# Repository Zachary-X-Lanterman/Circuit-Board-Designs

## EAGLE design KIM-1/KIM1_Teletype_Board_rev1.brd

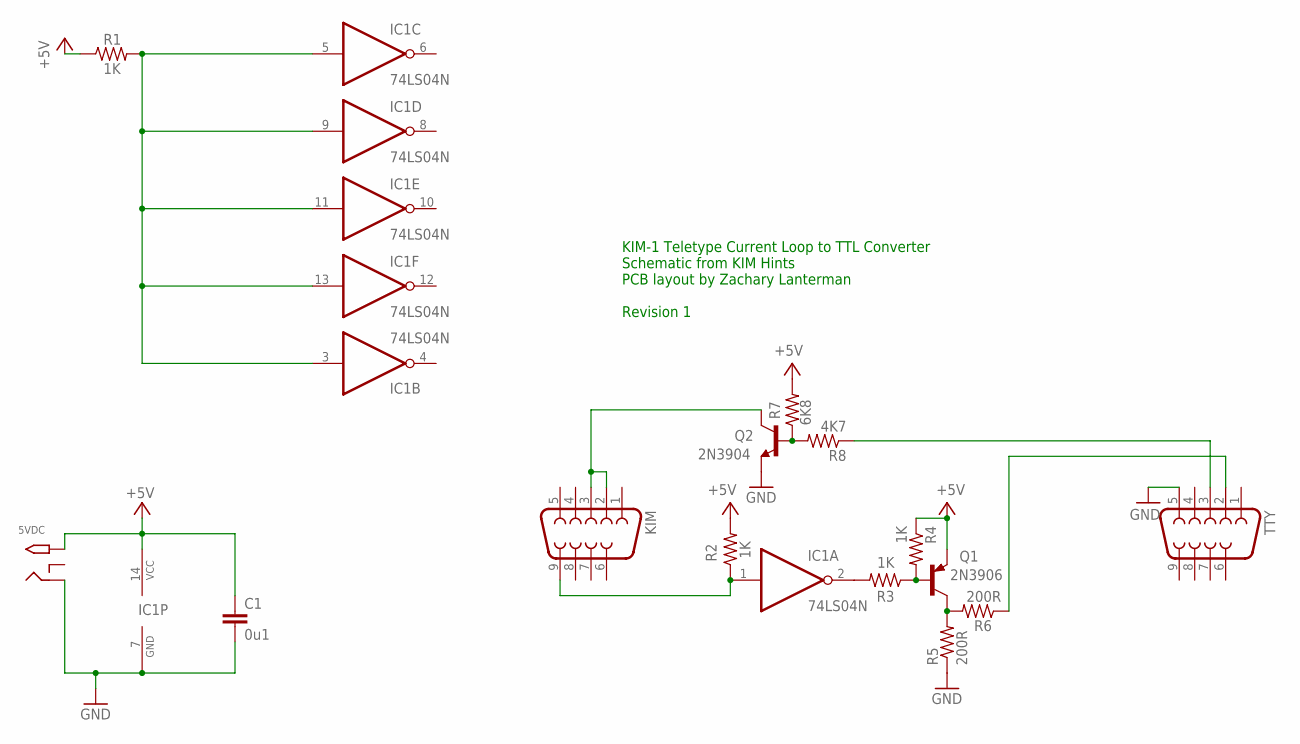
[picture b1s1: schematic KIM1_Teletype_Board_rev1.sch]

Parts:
5VDC: 2.1MMJACKTHM; PJ-102A
C1: 0u1; C050-025X075-AARON
IC1: 74LS04N; DIL14
KIM: F09HP
Q1: 2N3906; TO92
Q2: 2N3904; TO92
R1, R2, R3, R4: 1K; 0207/10
R5, R6: 200R; 0207/10
R7: 6K8; 0207/10
R8: 4K7; 0207/10
TTY: F09HP

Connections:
+5V: 5VDC.TIP, C1.1, IC1.14 (VCC), Q1.3 (E), R1.1, R2.2, R4.1, R7.2
GND: 5VDC.RING, C1.2, IC1.7 (GND), Q2.3 (E), R5.1, TTY.5
unnamed: IC1.2 (O), R3.2
unnamed: Q1.2 (B), R3.1, R4.2
unnamed: Q1.1 (C), R5.2, R6.2
unnamed: IC1.3 (I), IC1.5 (I), IC1.9 (I), IC1.11 (I), IC1.13 (I), R1.2
unnamed: R6.1, TTY.2
unnamed: KIM.2, KIM.3, Q2.1 (C)
unnamed: Q2.2 (B), R7.1, R8.2
unnamed: R8.1, TTY.3
U: IC1.1 (I), KIM.9, R2.1

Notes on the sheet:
KIM-1 Teletype Current Loop to TTL Converter Schematic from KIM Hints PCB layout by Zachary Lanterman Revision 1

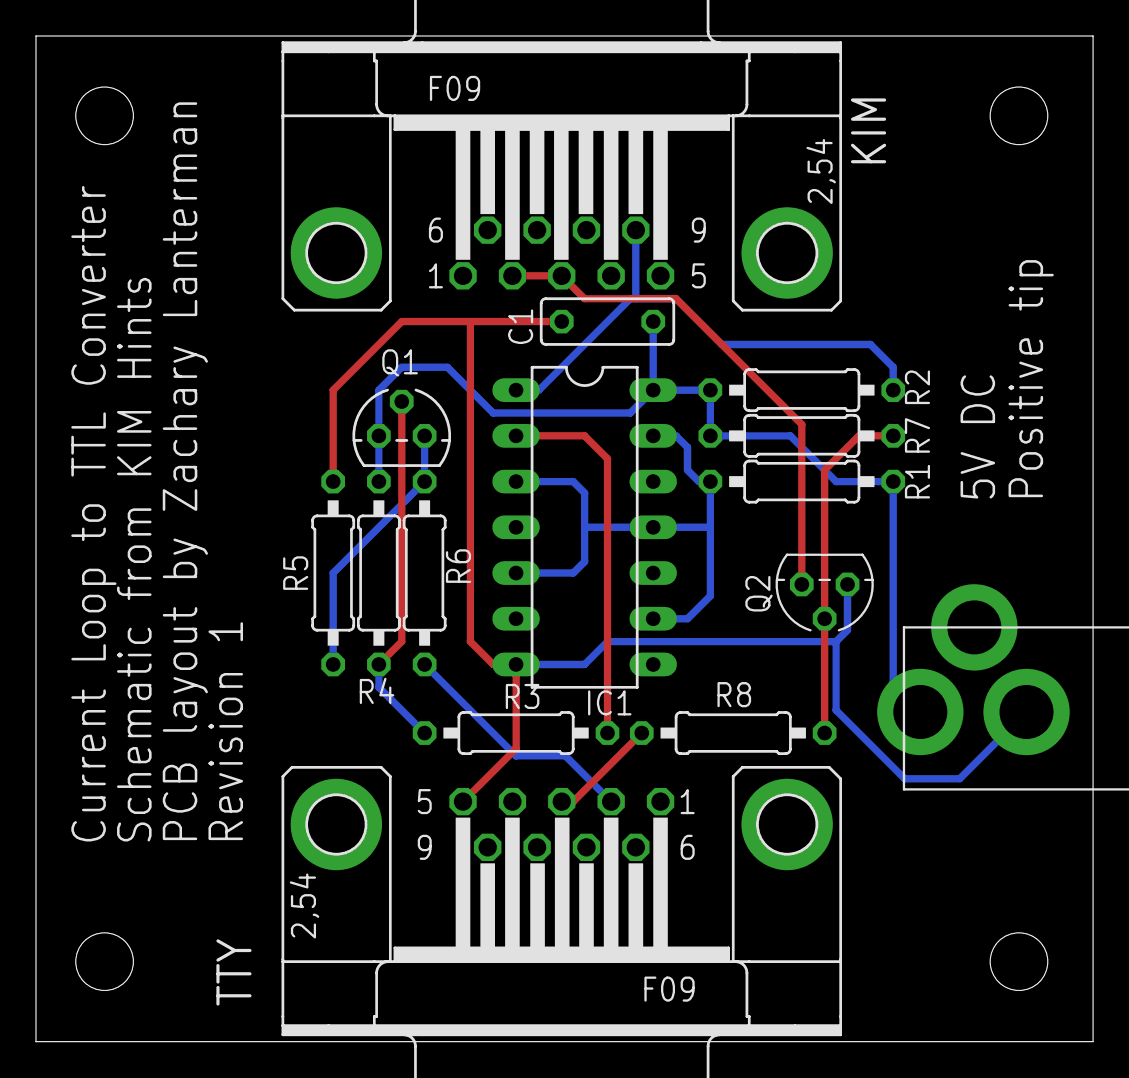
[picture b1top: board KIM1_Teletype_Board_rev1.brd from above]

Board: 2 copper layers, 58.7 x 55.9 mm, 15 parts (0 on the bottom side), 11 nets.

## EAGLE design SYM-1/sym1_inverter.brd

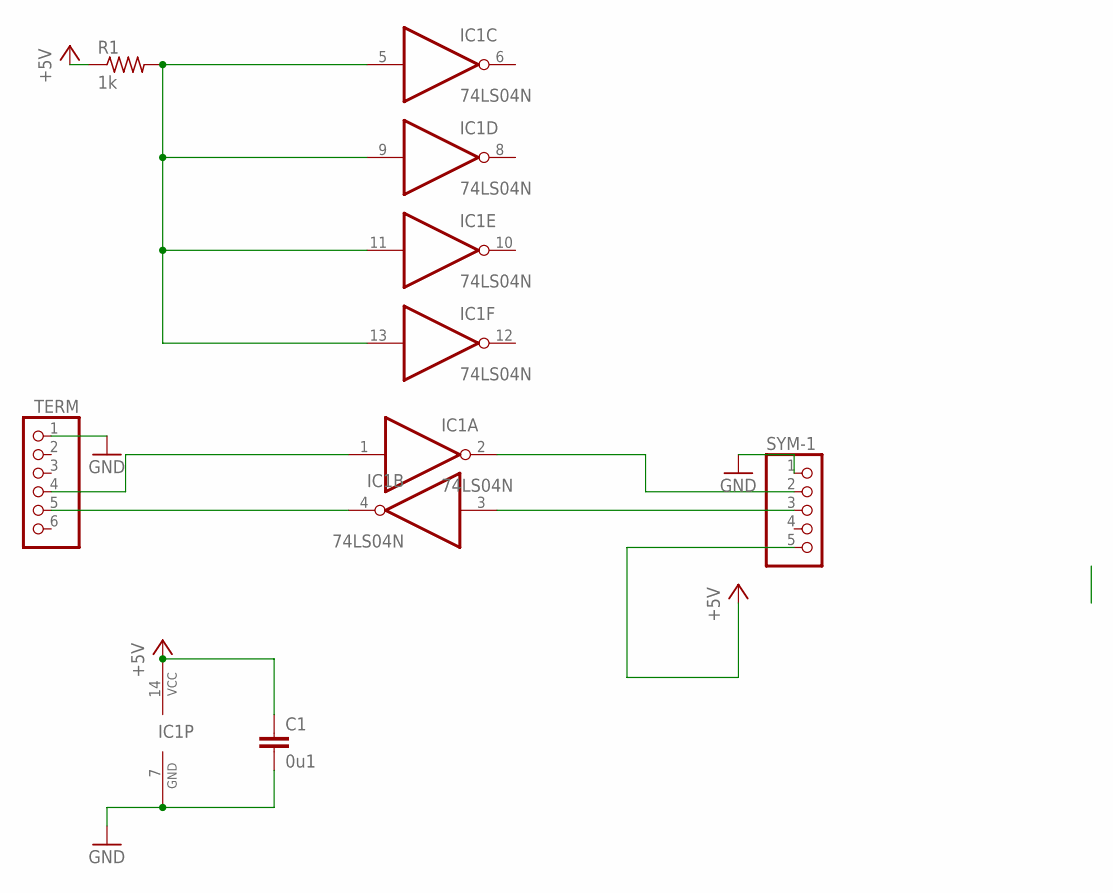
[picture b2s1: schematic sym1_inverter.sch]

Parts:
C1: 0u1; C050-025X075-AARON
IC1: 74LS04N; DIL14
R1: 1k; 0207/10
SYM-1: PINHD-1X5; 1X05
TERM: PINHD-1X6; 1X06

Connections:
+5V: C1.1, IC1.14 (VCC), R1.1, SYM-1.5
GND: C1.2, IC1.7 (GND), SYM-1.1, TERM.1
unnamed: IC1.2 (O), SYM-1.2
unnamed: IC1.3 (I), SYM-1.3
unnamed: IC1.4 (O), TERM.5
unnamed: IC1.1 (I), TERM.4
unnamed: IC1.5 (I), IC1.9 (I), IC1.11 (I), IC1.13 (I), R1.2

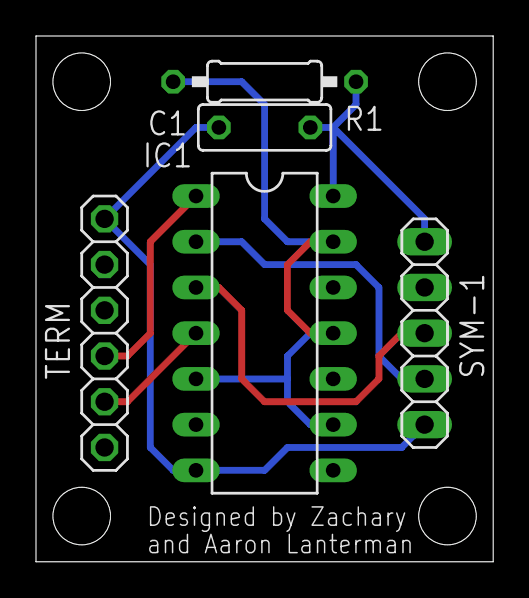
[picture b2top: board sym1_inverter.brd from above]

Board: 2 copper layers, 25.4 x 29.2 mm, 5 parts (0 on the bottom side), 7 nets.

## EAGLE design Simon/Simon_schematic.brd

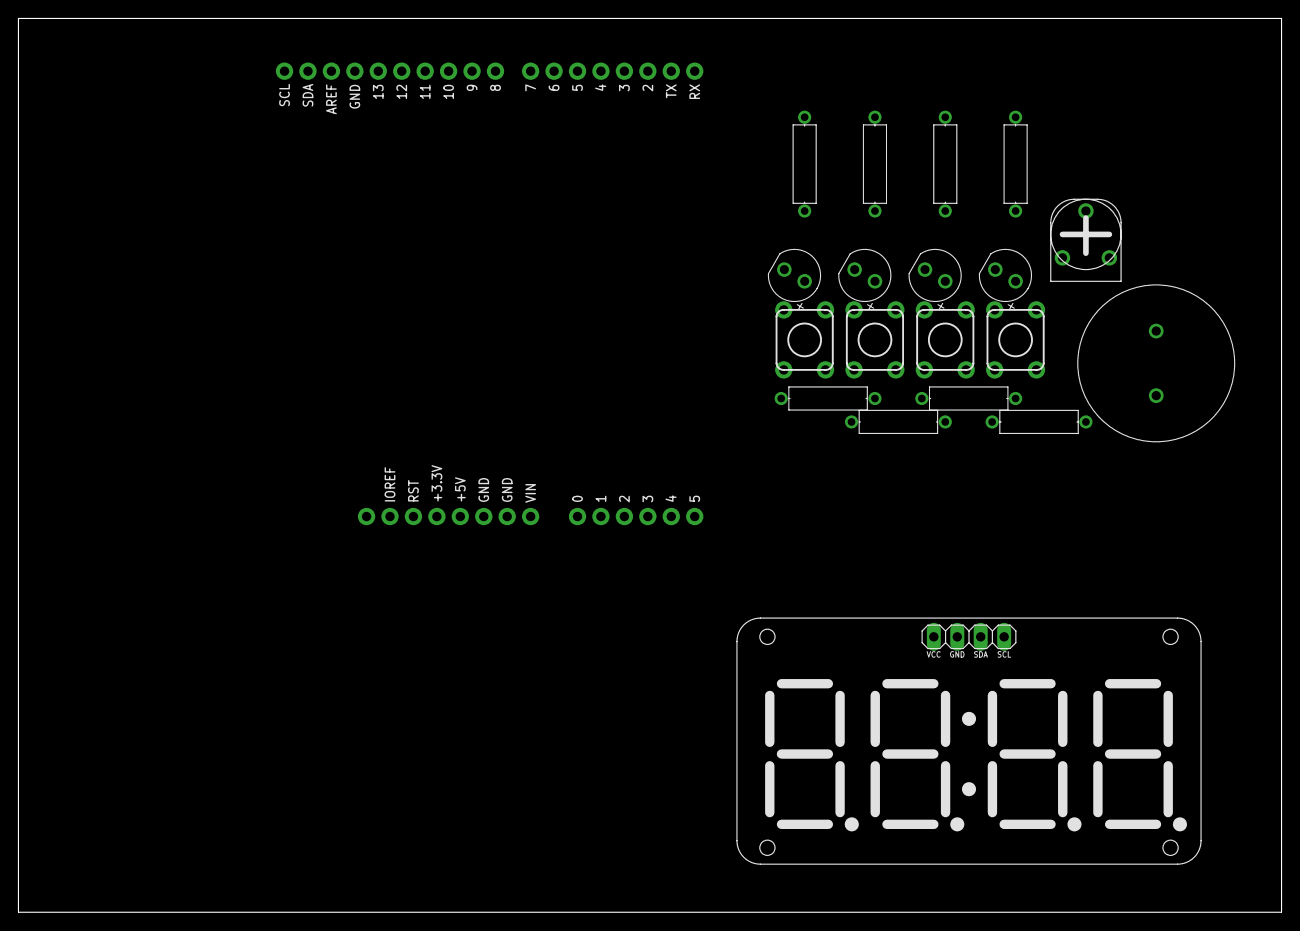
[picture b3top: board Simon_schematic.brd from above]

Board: 2 copper layers, 136.9 x 96.9 mm, 20 parts (0 on the bottom side), 18 nets, no tracks yet.

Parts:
D5: GREEN; LEDRD254W60D565H860B_G
D6: RED; LEDRD254W60D565H860B
D7: YELLOW; LEDRD254W60D565H860B_Y
D8: BLUE; LEDRD254W60D565H860B_B
PIEZO2: PIEZO
R9, R10, R11, R12: 10k; RESAD1016W63L850D250B
R13, R14, R15, R16: 100; RESAD1016W63L850D250B
RPOT2: 250k; HA-06-SM065
S5, S6, S7, S8: SWITCH_MOMENTARY; SWITCH-MOMENTARY-PTH-6.5MM
U2: ARDUINO-UNO-R3-SHIELD
U3: BLUE; 7SEG-X4-I2C

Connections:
D5_A: D5.1, R14.2
D6_A: D6.1, R13.2
D7_A: D7.1, R15.2
D8_A: D8.1, R16.2
U2_5V: RPOT2.1, S5.3, S5.4, S6.3, S6.4, S7.3, S7.4, S8.3, S8.4, U2.5V, U3.P$1
U2_A0: RPOT2.2, U2.A0
U2_D2: R13.1, U2.D2
U2_D3: R14.1, U2.D3
U2_D4: R15.1, U2.D4
U2_D5: R16.1, U2.D5
U2_D6: R9.1, S5.1, S5.2, U2.D6
U2_D7: R10.1, S6.1, S6.2, U2.D7
U2_D8: R11.1, S7.1, S7.2, U2.D8
U2_D9: R12.1, S8.1, S8.2, U2.D9
U2_D13: PIEZO2.1, U2.D13
U2_GND: D5.2, D6.2, D7.2, D8.2, PIEZO2.2, R9.2, R10.2, R11.2, R12.2, RPOT2.3, U2.GND@0, U2.GND@1, U2.GND@2, U3.P$2
U2_SCL: U2.SCL, U3.P$4
U2_SDA: U2.SDA, U3.P$3
